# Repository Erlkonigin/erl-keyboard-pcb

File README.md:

PCB for a 104 key, ANSI compacted layout. Additionally 6 media control buttons. Numpad moved to the left side.
Based on ATtmega AT32U4-AU MCU.  g g g g  gggggg g  gg  g  gg  gg  g                                 g                         g g                    rg e               s s

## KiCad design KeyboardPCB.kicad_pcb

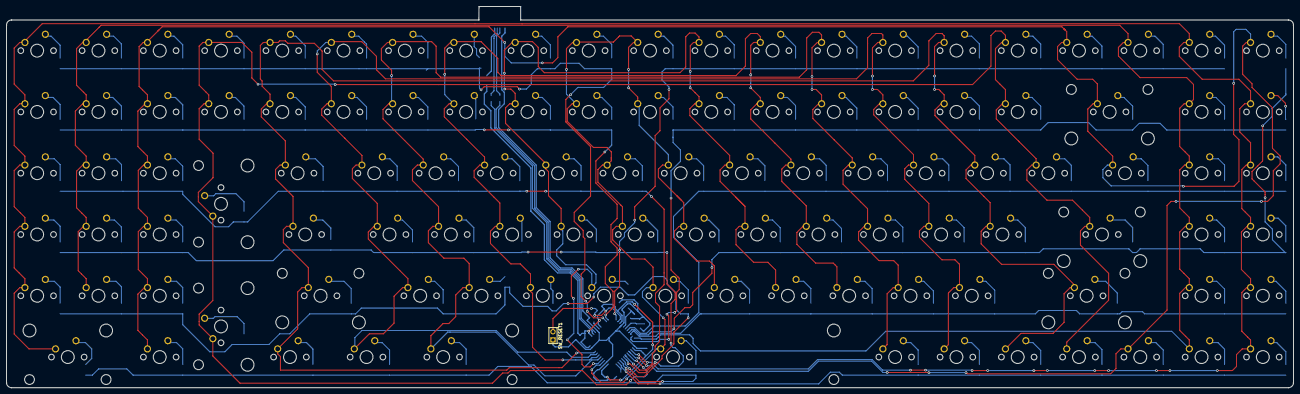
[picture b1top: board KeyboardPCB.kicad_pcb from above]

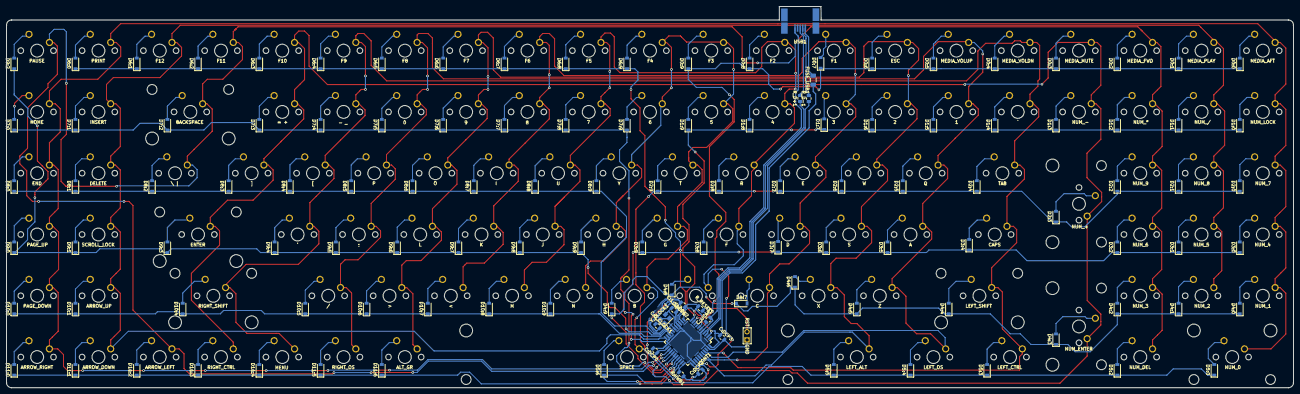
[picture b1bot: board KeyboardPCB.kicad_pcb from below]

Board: 2 copper layers, 400.1 x 118.5 mm, 236 parts (126 on the bottom side), 144 nets.

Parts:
C:0_CLOCK1, C:1_CLOCK2: 22pF; C_0805_2012Metric
C:DCP0, C:DCP1, C:DCP2: 0.1uF; C_0805_2012Metric
C:DCP3: 10uF; C_0805_2012Metric
CONT1: ATmega32U4-AU; TQFP-44_10x10mm_P0.8mm
C_UCAP1: 1uF; C_0805_2012Metric
D0:0, D0:1, D0:2, D0:3, D0:4, D0:5, D0:6, D0:7, D0:8, D0:9, D1:0, D1:1, D1:2, D1:3, D1:4, D1:5, D1:6, D1:7, D1:8, D1:9, D2:0, D2:1, D2:2, D2:3, D2:4, D2:5, D2:6, D2:7, D2:8, D2:9, D3:0, D3:1, D3:2, D3:4, D3:5, D3:6, D3:7, D3:8, D3:9, D4:0, D4:1, D4:2, D4:3, D4:4, D4:5, D4:6, D4:7, D4:8, D4:9, D5:0, D5:2, D5:3, D5:4, D5:5, D5:6, D6:0, D6:1, D6:2, D6:3, D6:4, D6:5, D6:6, D6:7, D6:8, D6:9, D7:0, D7:1, D7:2, D7:3, D7:4, D7:5, D7:6, D7:7, D7:8, D7:9, D8:0, D8:1, D8:2, D8:3, D8:4, D8:5, D8:6, D8:7, D8:8, D8:9, D9:0, D9:1, D9:2, D9:3, D9:4, D9:5, D9:6, D9:7, D9:8, D9:9, D10:0, D10:1, D10:4, D10:5, D10:6, D10:7, D10:8, D10:9, D11:0, D11:1, D11:2, D11:3, D11:4, D11:5, D11:6: SOD-123; D_SOD-123
FUSE_USB1: 500mA; Fuse_1206_3216Metric
MX0:0_AFT1: MEDIA_AFT; MXOnly-1U-NoLED
MX0:1_PLAY1: MEDIA_PLAY; MXOnly-1U-NoLED
MX0:2_FWD1: MEDIA_FWD; MXOnly-1U-NoLED
MX0:3_MUT1: MEDIA_MUTE; MXOnly-1U-NoLED
MX0:4_VOL-1: MEDIA_VOLDN; MXOnly-1U-NoLED
MX0:5_VOL+1: MEDIA_VOLUP; MXOnly-1U-NoLED
MX0:6_ESC1: ESC; MXOnly-1U-NoLED
MX0:7_F1: F1; MXOnly-1U-NoLED
MX0:8_F2: F2; MXOnly-1U-NoLED
MX0:9_F3: F3; MXOnly-1U-NoLED
MX1:0_NUM1: NUM_LOCK; MXOnly-1U-NoLED
MX1:1_NU/1: NUM_/; MXOnly-1U-NoLED
MX1:2_NU*1: NUM_*; MXOnly-1U-NoLED
MX1:3_NU-1: NUM_-; MXOnly-1U-NoLED
MX1:4_TIL1: `; MXOnly-1U-NoLED
MX1:5_1: 1; MXOnly-1U-NoLED
MX1:6_2: 2; MXOnly-1U-NoLED
MX1:7_3: 3; MXOnly-1U-NoLED
MX1:8_4: 4; MXOnly-1U-NoLED
MX1:9_5: 5; MXOnly-1U-NoLED
MX2:0_NU7: NUM_7; MXOnly-1U-NoLED
MX2:1_NU8: NUM_8; MXOnly-1U-NoLED
MX2:2_NU9: NUM_9; MXOnly-1U-NoLED
MX2:3_NU+1: NUM_+; MXOnly-2U-NoLED
MX2:4_TAB1: TAB; MXOnly-1.5U-NoLED
MX2:5_Q1: Q; MXOnly-1U-NoLED
MX2:6_W1: W; MXOnly-1U-NoLED
MX2:7_E1: E; MXOnly-1U-NoLED
MX2:8_R1: R; MXOnly-1U-NoLED
MX2:9_T1: T; MXOnly-1U-NoLED
MX3:0_NU4: NUM_4; MXOnly-1U-NoLED
MX3:1_NU5: NUM_5; MXOnly-1U-NoLED
MX3:2_NU6: NUM_6; MXOnly-1U-NoLED
MX3:4_CAP1: CAPS; MXOnly-1.75U-NoLED
MX3:5_A1: A; MXOnly-1U-NoLED
MX3:6_S1: S; MXOnly-1U-NoLED
MX3:7_D1: D; MXOnly-1U-NoLED
MX3:8_F1: F; MXOnly-1U-NoLED
MX3:9_G1: G; MXOnly-1U-NoLED
MX4:0_NU1: NUM_1; MXOnly-1U-NoLED
MX4:1_NU2: NUM_2; MXOnly-1U-NoLED
MX4:2_NU3: NUM_3; MXOnly-1U-NoLED
MX4:3_NEN1: NUM_ENTER; MXOnly-2U-NoLED
MX4:4_LSH1: LEFT_SHIFT; MXOnly-2.25U-NoLED
MX4:5_Z1: Z; MXOnly-1U-NoLED
MX4:6_X1: X; MXOnly-1U-NoLED
MX4:7_C1: C; MXOnly-1U-NoLED
MX4:8_V1: V; MXOnly-1U-NoLED
MX4:9_B1: B; MXOnly-1U-NoLED
MX5:0_NU0: NUM_0; MXOnly-2U-ReversedStabilizers-NoLED
MX5:2_NUD1: NUM_DEL; MXOnly-1U-NoLED
MX5:3_LCT1: LEFT_CTRL; MXOnly-1.25U-NoLED
MX5:4_OS1: LEFT_OS; MXOnly-1.25U-NoLED
MX5:5_LAL1: LEFT_ALT; MXOnly-1.25U-NoLED
MX5:9_SPC1: SPACE; MXOnly-6.25U-ReversedStabilizers-NoLED
MX6:0_PRT1: PRINT; MXOnly-1U-NoLED
MX6:1_F12: F12; MXOnly-1U-NoLED
MX6:2_F11: F11; MXOnly-1U-NoLED
MX6:3_F10: F10; MXOnly-1U-NoLED
MX6:4_F9: F9; MXOnly-1U-NoLED
MX6:5_F8: F8; MXOnly-1U-NoLED
MX6:6_F7: F7; MXOnly-1U-NoLED
MX6:7_F6: F6; MXOnly-1U-NoLED
MX6:8_F5: F5; MXOnly-1U-NoLED
MX6:9_F4: F4; MXOnly-1U-NoLED
MX7:0_HOM1: HOME; MXOnly-1U-NoLED
MX7:1_INS1: INSERT; MXOnly-1U-NoLED
MX7:2_BSP1: BACKSPACE; MXOnly-2U-NoLED
MX7:3_=1: = +; MXOnly-1U-NoLED
MX7:4_-1: - _; MXOnly-1U-NoLED
MX7:5_0: 0; MXOnly-1U-NoLED
MX7:6_9: 9; MXOnly-1U-NoLED
MX7:7_8: 8; MXOnly-1U-NoLED
MX7:8_7: 7; MXOnly-1U-NoLED
MX7:9_6: 6; MXOnly-1U-NoLED
MX8:0_END1: END; MXOnly-1U-NoLED
MX8:1_DEL1: DELETE; MXOnly-1U-NoLED
MX8:2_\1: \ |; MXOnly-1U-NoLED
MX8:3_]1: ]; MXOnly-1U-NoLED
MX8:4_[1: [; MXOnly-1U-NoLED
MX8:5_P1: P; MXOnly-1U-NoLED
MX8:6_O1: O; MXOnly-1U-NoLED
MX8:7_I1: I; MXOnly-1U-NoLED
MX8:8_U1: U; MXOnly-1U-NoLED
MX8:9_Y1: Y; MXOnly-1U-NoLED
MX9:0_PGU1: PAGE_UP; MXOnly-1U-NoLED
MX9:1_SLK1: SCROLL_LOCK; MXOnly-1U-NoLED
MX9:2_PUS1: PAUSE; MXOnly-1U-NoLED
MX9:3_ENT1: ENTER; MXOnly-2.25U-NoLED
MX9:4_'1: '; MXOnly-1U-NoLED
MX9:5_;1: ;; MXOnly-1U-NoLED
MX9:6_L1: L; MXOnly-1U-NoLED
MX9:7_K1: K; MXOnly-1U-NoLED
MX9:8_J1: J; MXOnly-1U-NoLED
MX9:9_H1: H; MXOnly-1U-NoLED
MX10:0_PGU1: PAGE_DOWN; MXOnly-1U-NoLED
MX10:1_UP1: ARROW_UP; MXOnly-1U-NoLED
MX10:4_RSH1: RIGHT_SHIFT; MXOnly-2.75U-NoLED
MX10:5_/1: /; MXOnly-1U-NoLED
MX10:6_.1: >; MXOnly-1U-NoLED
MX10:7_,1: <; MXOnly-1U-NoLED
MX10:8_M1: M; MXOnly-1U-NoLED
MX10:9_N1: N; MXOnly-1U-NoLED
MX11:0_RGT1: ARROW_RIGHT; MXOnly-1U-NoLED
MX11:1_DWN1: ARROW_DOWN; MXOnly-1U-NoLED
MX11:2_LFT1: ARROW_LEFT; MXOnly-1U-NoLED
MX11:3_RCT1: RIGHT_CTRL; MXOnly-1U-NoLED
MX11:4_MEN1: MENU; MXOnly-1U-NoLED
MX11:5_OS1: RIGHT_OS; MXOnly-1U-NoLED
MX11:6_AGR1: ALT_GR; MXOnly-1U-NoLED
R:HWB1: 10k; R_0805_2012Metric
R_D+1: 22; R_0805_2012Metric
R_D-1: 22; R_0805_2012Metric
R_RESET1: 10k; R_0805_2012Metric
SW_RESET1: SW_Push; Reset_Pretty_2pin
USB1: Molex-0548190572
Y_CLOCK1: 16MHz; Crystal_SMD_3225-4Pin_3.2x2.5mm

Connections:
+5V: C:DCP0.1, C:DCP1.1, C:DCP2.1, C:DCP3.1, CONT1.2, CONT1.7, CONT1.14, CONT1.24, CONT1.34, CONT1.44, FUSE_USB1.1, R_RESET1.1
COL0: CONT1.25, MX0:0_AFT1.1, MX1:0_NUM1.1, MX2:0_NU7.1, MX3:0_NU4.1, MX4:0_NU1.1, MX5:0_NU0.1, MX6:0_PRT1.1, MX7:0_HOM1.1, MX8:0_END1.1, MX9:0_PGU1.1, MX10:0_PGU1.1, MX11:0_RGT1.1
COL1: CONT1.22, MX0:1_PLAY1.1, MX1:1_NU/1.1, MX2:1_NU8.1, MX3:1_NU5.1, MX4:1_NU2.1, MX6:1_F12.1, MX7:1_INS1.1, MX8:1_DEL1.1, MX9:1_SLK1.1, MX10:1_UP1.1, MX11:1_DWN1.1
COL2: CONT1.26, MX0:2_FWD1.1, MX1:2_NU*1.1, MX2:2_NU9.1, MX3:2_NU6.1, MX4:2_NU3.1, MX5:2_NUD1.1, MX6:2_F11.1, MX7:2_BSP1.1, MX8:2_\1.1, MX9:2_PUS1.1, MX11:2_LFT1.1
COL3: CONT1.27, MX0:3_MUT1.1, MX1:3_NU-1.1, MX2:3_NU+1.1, MX4:3_NEN1.1, MX6:3_F10.1, MX7:3_=1.1, MX8:3_]1.1, MX9:3_ENT1.1, MX11:3_RCT1.1
COL4: CONT1.41, MX0:4_VOL-1.1, MX1:4_TIL1.1, MX2:4_TAB1.1, MX3:4_CAP1.1, MX4:4_LSH1.1, MX5:3_LCT1.1, MX6:4_F9.1, MX7:4_-1.1, MX8:4_[1.1, MX9:4_'1.1, MX10:4_RSH1.1, MX11:4_MEN1.1
COL5: CONT1.40, MX0:5_VOL+1.1, MX1:5_1.1, MX2:5_Q1.1, MX3:5_A1.1, MX4:5_Z1.1, MX5:4_OS1.1, MX6:5_F8.1, MX7:5_0.1, MX8:5_P1.1, MX9:5_;1.1, MX10:5_/1.1, MX11:5_OS1.1
COL6: CONT1.38, MX0:6_ESC1.1, MX1:6_2.1, MX2:6_W1.1, MX3:6_S1.1, MX4:6_X1.1, MX5:5_LAL1.1, MX6:6_F7.1, MX7:6_9.1, MX8:6_O1.1, MX9:6_L1.1, MX10:6_.1.1, MX11:6_AGR1.1
COL7: CONT1.39, MX0:7_F1.1, MX1:7_3.1, MX2:7_E1.1, MX3:7_D1.1, MX4:7_C1.1, MX6:7_F6.1, MX7:7_8.1, MX8:7_I1.1, MX9:7_K1.1, MX10:7_,1.1
COL8: CONT1.37, MX0:8_F2.1, MX1:8_4.1, MX2:8_R1.1, MX3:8_F1.1, MX4:8_V1.1, MX6:8_F5.1, MX7:8_7.1, MX8:8_U1.1, MX9:8_J1.1, MX10:8_M1.1
COL9: CONT1.36, MX0:9_F3.1, MX1:9_5.1, MX2:9_T1.1, MX3:9_G1.1, MX4:9_B1.1, MX5:9_SPC1.1, MX6:9_F4.1, MX7:9_6.1, MX8:9_Y1.1, MX9:9_H1.1, MX10:9_N1.1
D+: R_D+1.2, USB1.3
D-: R_D-1.2, USB1.4
GND: C:0_CLOCK1.2, C:1_CLOCK2.2, C:DCP0.2, C:DCP1.2, C:DCP2.2, C:DCP3.2, CONT1.5, CONT1.15, CONT1.23, CONT1.35, CONT1.43, C_UCAP1.2, R:HWB1.1, SW_RESET1.1, USB1.1, Y_CLOCK1.2, Y_CLOCK1.4
unnamed: C:0_CLOCK1.1, CONT1.17, Y_CLOCK1.1
unnamed: C:1_CLOCK2.1, CONT1.16, Y_CLOCK1.3
unnamed: CONT1.3, R_D-1.1
unnamed: CONT1.4, R_D+1.1
unnamed: CONT1.6, C_UCAP1.1
unnamed: CONT1.13, R_RESET1.2, SW_RESET1.2
unnamed: CONT1.33, R:HWB1.2
unnamed: D0:0.2, MX0:0_AFT1.2
unnamed: D0:1.2, MX0:1_PLAY1.2
unnamed: D0:2.2, MX0:2_FWD1.2
unnamed: D0:3.2, MX0:3_MUT1.2
unnamed: D0:4.2, MX0:4_VOL-1.2
unnamed: D0:5.2, MX0:5_VOL+1.2
unnamed: D0:6.2, MX0:6_ESC1.2
unnamed: D0:7.2, MX0:7_F1.2
unnamed: D0:8.2, MX0:8_F2.2
unnamed: D0:9.2, MX0:9_F3.2
unnamed: D1:0.2, MX1:0_NUM1.2
unnamed: D1:1.2, MX1:1_NU/1.2
unnamed: D1:2.2, MX1:2_NU*1.2
unnamed: D1:3.2, MX1:3_NU-1.2
unnamed: D1:4.2, MX1:4_TIL1.2
unnamed: D1:5.2, MX1:5_1.2
unnamed: D1:6.2, MX1:6_2.2
unnamed: D1:7.2, MX1:7_3.2
unnamed: D1:8.2, MX1:8_4.2
unnamed: D1:9.2, MX1:9_5.2
unnamed: D2:0.2, MX2:0_NU7.2
unnamed: D2:1.2, MX2:1_NU8.2
unnamed: D2:2.2, MX2:2_NU9.2
unnamed: D2:3.2, MX2:3_NU+1.2
unnamed: D2:4.2, MX2:4_TAB1.2
unnamed: D2:5.2, MX2:5_Q1.2
unnamed: D2:6.2, MX2:6_W1.2
unnamed: D2:7.2, MX2:7_E1.2
unnamed: D2:8.2, MX2:8_R1.2
unnamed: D2:9.2, MX2:9_T1.2
unnamed: D3:0.2, MX3:0_NU4.2
unnamed: D3:1.2, MX3:1_NU5.2
unnamed: D3:2.2, MX3:2_NU6.2
unnamed: D3:4.2, MX3:4_CAP1.2
unnamed: D3:5.2, MX3:5_A1.2
unnamed: D3:6.2, MX3:6_S1.2
unnamed: D3:7.2, MX3:7_D1.2
unnamed: D3:8.2, MX3:8_F1.2
unnamed: D3:9.2, MX3:9_G1.2
unnamed: D4:0.2, MX4:0_NU1.2
unnamed: D4:1.2, MX4:1_NU2.2
unnamed: D4:2.2, MX4:2_NU3.2
unnamed: D4:3.2, MX4:3_NEN1.2
unnamed: D4:4.2, MX4:4_LSH1.2
unnamed: D4:5.2, MX4:5_Z1.2
unnamed: D4:6.2, MX4:6_X1.2
unnamed: D4:7.2, MX4:7_C1.2
unnamed: D4:8.2, MX4:8_V1.2
unnamed: D4:9.2, MX4:9_B1.2
unnamed: D5:0.2, MX5:0_NU0.2
unnamed: D5:2.2, MX5:2_NUD1.2
unnamed: D5:3.2, MX5:3_LCT1.2
unnamed: D5:4.2, MX5:4_OS1.2
unnamed: D5:5.2, MX5:5_LAL1.2
unnamed: D5:6.2, MX5:9_SPC1.2
unnamed: D6:0.2, MX6:0_PRT1.2
unnamed: D6:1.2, MX6:1_F12.2
unnamed: D6:2.2, MX6:2_F11.2
unnamed: D6:3.2, MX6:3_F10.2
unnamed: D6:4.2, MX6:4_F9.2
unnamed: D6:5.2, MX6:5_F8.2
unnamed: D6:6.2, MX6:6_F7.2
unnamed: D6:7.2, MX6:7_F6.2
unnamed: D6:8.2, MX6:8_F5.2
unnamed: D6:9.2, MX6:9_F4.2
unnamed: D7:0.2, MX7:0_HOM1.2
unnamed: D7:1.2, MX7:1_INS1.2
unnamed: D7:2.2, MX7:2_BSP1.2
unnamed: D7:3.2, MX7:3_=1.2
unnamed: D7:4.2, MX7:4_-1.2
unnamed: D7:5.2, MX7:5_0.2
unnamed: D7:6.2, MX7:6_9.2
unnamed: D7:7.2, MX7:7_8.2
unnamed: D7:8.2, MX7:8_7.2
unnamed: D7:9.2, MX7:9_6.2
unnamed: D8:0.2, MX8:0_END1.2
unnamed: D8:1.2, MX8:1_DEL1.2
unnamed: D8:2.2, MX8:2_\1.2
unnamed: D8:3.2, MX8:3_]1.2
unnamed: D8:4.2, MX8:4_[1.2
unnamed: D8:5.2, MX8:5_P1.2
unnamed: D8:6.2, MX8:6_O1.2
unnamed: D8:7.2, MX8:7_I1.2
unnamed: D8:8.2, MX8:8_U1.2
unnamed: D8:9.2, MX8:9_Y1.2
unnamed: D9:0.2, MX9:0_PGU1.2
unnamed: D9:1.2, MX9:1_SLK1.2
unnamed: D9:2.2, MX9:2_PUS1.2
unnamed: D9:3.2, MX9:3_ENT1.2
unnamed: D9:4.2, MX9:4_'1.2
unnamed: D9:5.2, MX9:5_;1.2
unnamed: D9:6.2, MX9:6_L1.2
unnamed: D9:7.2, MX9:7_K1.2
unnamed: D9:8.2, MX9:8_J1.2
unnamed: D9:9.2, MX9:9_H1.2
unnamed: D10:0.2, MX10:0_PGU1.2
unnamed: D10:1.2, MX10:1_UP1.2
unnamed: D10:4.2, MX10:4_RSH1.2
unnamed: D10:5.2, MX10:5_/1.2
unnamed: D10:6.2, MX10:6_.1.2
unnamed: D10:7.2, MX10:7_,1.2
unnamed: D10:8.2, MX10:8_M1.2
unnamed: D10:9.2, MX10:9_N1.2
unnamed: D11:0.2, MX11:0_RGT1.2
unnamed: D11:1.2, MX11:1_DWN1.2
unnamed: D11:2.2, MX11:2_LFT1.2
unnamed: D11:3.2, MX11:3_RCT1.2
unnamed: D11:4.2, MX11:4_MEN1.2
unnamed: D11:5.2, MX11:5_OS1.2
unnamed: D11:6.2, MX11:6_AGR1.2
ROW0: CONT1.10, D0:0.1, D0:1.1, D0:2.1, D0:3.1, D0:4.1, D0:5.1, D0:6.1, D0:7.1, D0:8.1, D0:9.1
ROW1: CONT1.11, D1:0.1, D1:1.1, D1:2.1, D1:3.1, D1:4.1, D1:5.1, D1:6.1, D1:7.1, D1:8.1, D1:9.1
ROW2: CONT1.28, D2:0.1, D2:1.1, D2:2.1, D2:3.1, D2:4.1, D2:5.1, D2:6.1, D2:7.1, D2:8.1, D2:9.1
ROW3: CONT1.29, D3:0.1, D3:1.1, D3:2.1, D3:4.1, D3:5.1, D3:6.1, D3:7.1, D3:8.1, D3:9.1
ROW4: CONT1.30, D4:0.1, D4:1.1, D4:2.1, D4:3.1, D4:4.1, D4:5.1, D4:6.1, D4:7.1, D4:8.1, D4:9.1
ROW5: CONT1.31, D5:0.1, D5:2.1, D5:3.1, D5:4.1, D5:5.1, D5:6.1
ROW6: CONT1.12, D6:0.1, D6:1.1, D6:2.1, D6:3.1, D6:4.1, D6:5.1, D6:6.1, D6:7.1, D6:8.1, D6:9.1
ROW7: CONT1.21, D7:0.1, D7:1.1, D7:2.1, D7:3.1, D7:4.1, D7:5.1, D7:6.1, D7:7.1, D7:8.1, D7:9.1
ROW8: CONT1.18, D8:0.1, D8:1.1, D8:2.1, D8:3.1, D8:4.1, D8:5.1, D8:6.1, D8:7.1, D8:8.1, D8:9.1
ROW9: CONT1.19, D9:0.1, D9:1.1, D9:2.1, D9:3.1, D9:4.1, D9:5.1, D9:6.1, D9:7.1, D9:8.1, D9:9.1
ROW10: CONT1.20, D10:0.1, D10:1.1, D10:4.1, D10:5.1, D10:6.1, D10:7.1, D10:8.1, D10:9.1
ROW11: CONT1.32, D11:0.1, D11:1.1, D11:2.1, D11:3.1, D11:4.1, D11:5.1, D11:6.1
VCC: FUSE_USB1.2, USB1.5

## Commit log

2020-06-14 README edits
2020-06-14 Added initial kicad files
2020-06-14 Added ai03's submodules
2020-06-14 added schematic and footprint libraries
2020-06-14 Added elements to PCB schematics
2020-06-14 Added footprints
2020-06-14 Placed footprints
2020-06-14 routed switches
2020-06-14 Routing
2020-06-15 Corrected pads, rerouting start
2020-06-15 Footprint fixes
2020-06-15 Traced switches
2020-06-15 Tracing complete. Added outlines
2020-06-15 fixes
2020-06-16 created custom library, added reset footprint to there
2020-06-16 minor changes, added bom files
2020-06-16 minor changes
2020-06-16 Added silkscreen button designations
2020-06-16 routing fixes
2020-06-16 Changed switch footprint to mx only, general tidy up
2020-06-16 further trace fixes
2020-06-17 added new usb footprint, attached it
2020-07-09 finishing touches
